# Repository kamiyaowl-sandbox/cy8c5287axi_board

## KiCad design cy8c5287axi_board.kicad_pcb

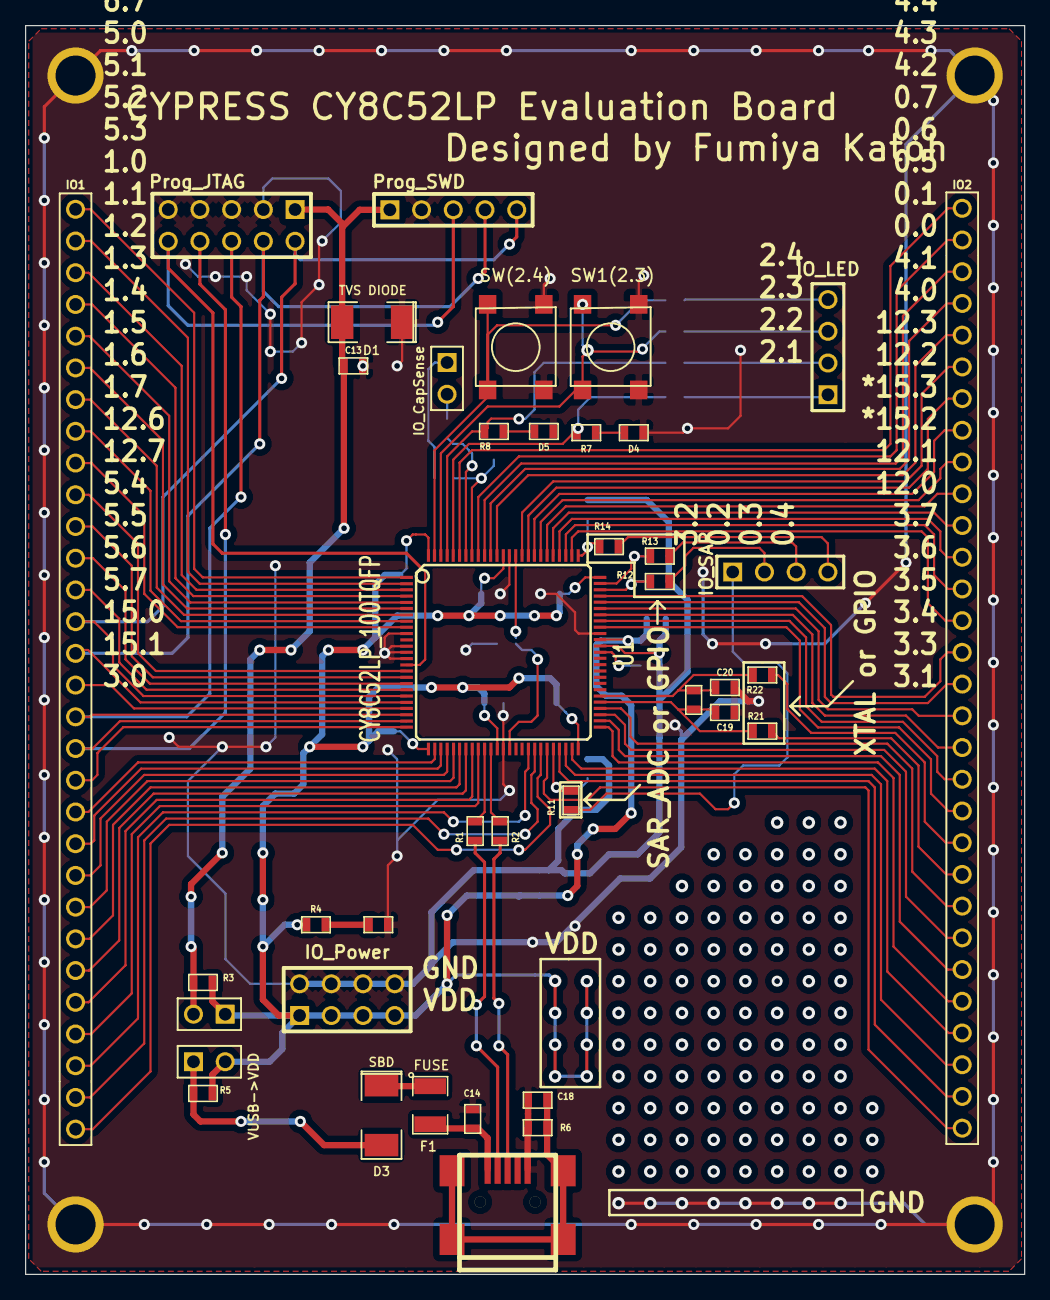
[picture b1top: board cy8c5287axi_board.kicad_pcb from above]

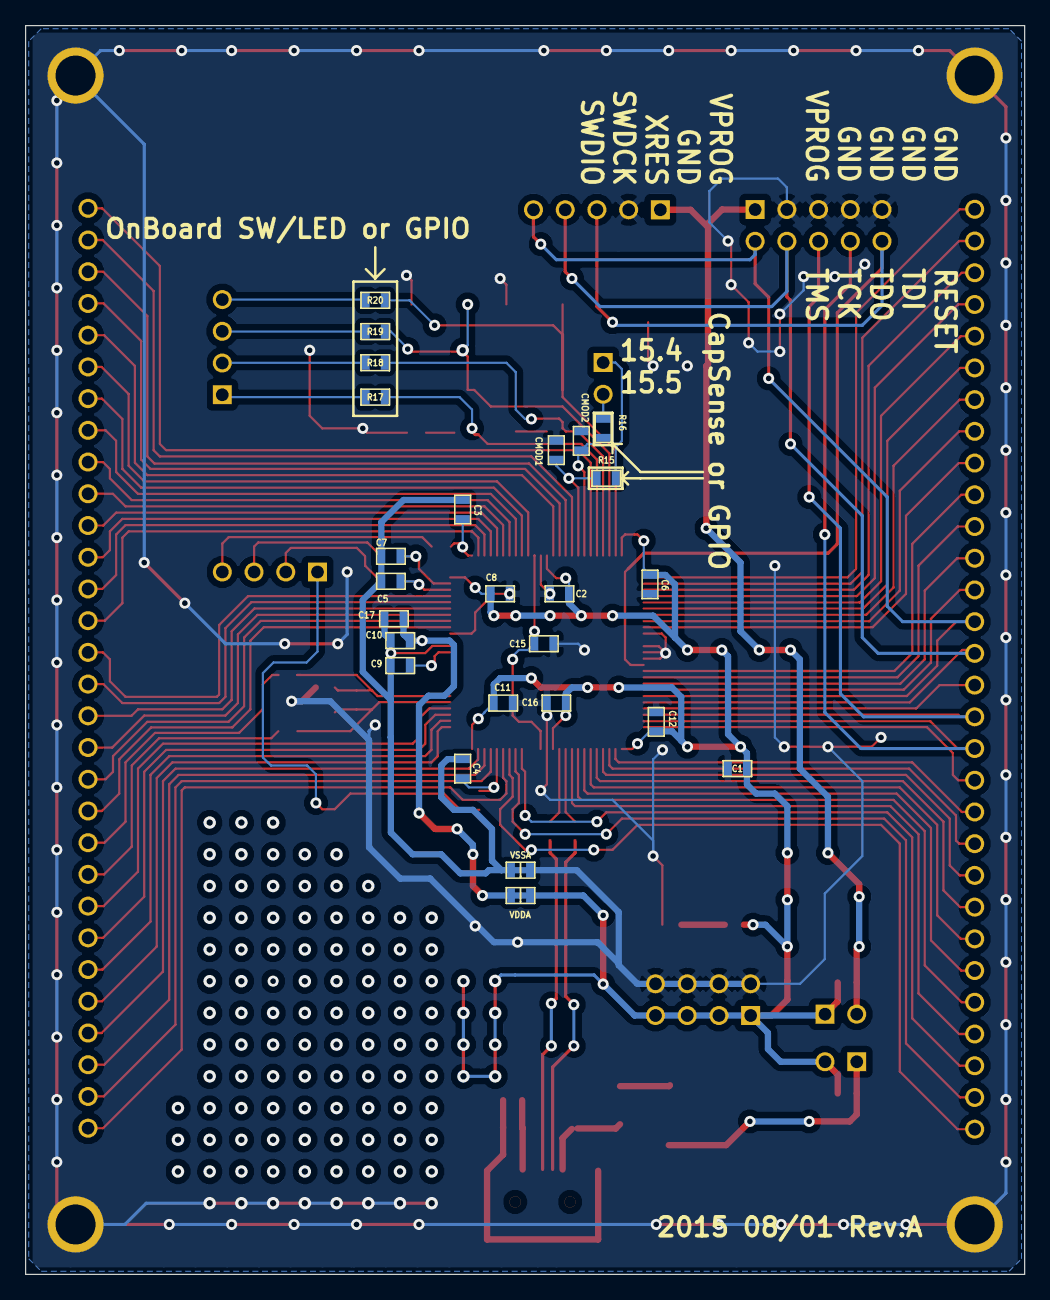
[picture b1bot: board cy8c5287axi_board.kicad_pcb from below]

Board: 2 copper layers, 80.0 x 100.0 mm, 61 parts (25 on the bottom side), 98 nets.

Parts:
C1, C3, C4, C5, C7, C9, C15, C17: 1u; SM0603
C2, C6, C8, C10, C11, C12, C13, C14, C16: 0.1u; SM0603
C18: 0.01u; SM0603
C19, C20: 22p; SM0603
CMOD1, CMOD2: 2200P; SM0603
D1: TVS DIODE; SM2010
D3: SBD; SM2010
D4: LED(2.1); SM0603
D5: LED(2.2); SM0603
F1: FUSE; SM1210
IO1, IO2: PIN_ARRAY_30
IO_CapSense: PIN_ARRAY_2X1
IO_LED: PIN_ARRAY_4x1
IO_Power: pin_array_4x2
IO_SAR: PIN_ARRAY_4x1
Prog_JTAG: PIN_ARRAY_5x2
Prog_SWD: PIN_ARRAY_5x1
R1, R2: 22; SM0603
R3, R5, R11, R12, R13, R14, R15, R16, R17, R18, R19, R20, R21, R22: 0; SM0603
R4: SM0603
R6: 100k; SM0603
R7, R8: R; SM0603
SW1(2.3): TSHA-T-2
SW(2.4): TSHA-T-2
U1: CY8C52LP_100TQFP; 100TQFP
VDDA: SM0603_Contact
VSSA: SM0603_Contact
VUSB->VDD: PIN_ARRAY_2X1

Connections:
/0.0: IO2.15, U1.71
/0.1: IO2.16, U1.72
/0.2*: C5.1, R12.1, U1.73
/0.3*: C7.1, R13.1, U1.74
/0.4*: C3.1, R14.1, U1.76
/0.5: IO2.17, U1.77
/0.6: IO2.18, U1.78
/0.7: IO2.19, U1.79
/1.0: IO1.14, Prog_JTAG.2, Prog_SWD.5, U1.20
/1.1: IO1.15, Prog_JTAG.4, Prog_SWD.4, U1.21
/1.2: IO1.16, U1.22
/1.3: IO1.17, Prog_JTAG.6, U1.23
/1.4: IO1.18, Prog_JTAG.8, U1.24
/1.5: IO1.19, U1.25
/1.6: IO1.20, U1.27
/1.7: IO1.21, U1.28
/2.0: IO2.30, U1.95
/2.1+: R7.1, R17.1, U1.96
/2.2+: R8.1, R18.1, U1.97
/2.3+: R19.1, SW1(2.3).1, U1.98
/2.4+: R20.1, SW(2.4).1, U1.99
/2.5: IO1.1, U1.1
/2.6: IO1.2, U1.2
/2.7: IO1.3, U1.3
/3.0: IO1.30, U1.44
/3.1: IO2.1, U1.45
/3.2*: C4.1, R11.1, U1.46
/3.3: IO2.2, U1.47
/3.4: IO2.3, U1.48
/3.5: IO2.4, U1.49
/3.6: IO2.5, U1.51
/3.7: IO2.6, U1.52
/4.0: IO2.13, U1.69
/4.1: IO2.14, U1.70
/4.2: IO2.20, U1.80
/4.3: IO2.21, U1.81
/4.4: IO2.22, U1.82
/4.5: IO2.23, U1.83
/4.6: IO2.24, U1.84
/4.7: IO2.25, U1.85
/5.0: IO1.10, U1.16
/5.1: IO1.11, U1.17
/5.2: IO1.12, U1.18
/5.3: IO1.13, U1.19
/5.4: IO1.24, U1.31
/5.5: IO1.25, U1.32
/5.6: IO1.26, U1.33
/5.7: IO1.27, U1.34
/6.0: IO2.26, U1.89
/6.1: IO2.27, U1.90
/6.2: IO2.28, U1.91
/6.3: IO2.29, U1.92
/6.4: IO1.6, U1.6
/6.5: IO1.7, U1.7
/6.6: IO1.8, U1.8
/6.7: IO1.9, U1.9
/12.0: IO2.7, U1.53
/12.1: IO2.8, U1.54
/12.2: IO2.11, U1.67
/12.3: IO2.12, U1.68
/12.4: IO1.4, U1.4
/12.5: IO1.5, U1.5
/12.6: IO1.22, U1.29
/12.7: IO1.23, U1.30
/15.0: IO1.28, U1.42
/15.1: IO1.29, U1.43
/15.2*: IO2.9, R21.1
/15.3*: IO2.10, R22.1
/15.4*: CMOD1.1, R15.1, U1.93
/15.5*: CMOD2.1, R16.1, U1.94
/15.6*: R1.1, U1.35
/15.7*: R2.1, U1.36
//XRES: Prog_JTAG.10, Prog_SWD.3, U1.15
/kHz_XI: C20.1, R22.2, U1.56
/kHz_XO: C19.1, R21.2, U1.55
unnamed: D4.1, R7.2
unnamed: D5.1, R8.2
unnamed: IO_CapSense.1, R15.2
unnamed: IO_CapSense.2, R16.2
unnamed: IO_LED.1, R17.2
unnamed: IO_LED.2, R18.2
unnamed: IO_LED.3, R19.2
unnamed: IO_LED.4, R20.2
unnamed: IO_SAR.4, R14.2
unnamed: IO_SAR.1, R11.2
unnamed: IO_SAR.2, R12.2
unnamed: IO_SAR.3, R13.2
unnamed: D3.2, R5.2, VUSB->VDD.1
unnamed: D3.1, F1.1
unnamed: C14.1, F1.2
unnamed: C18.1, R6.1
VCCA: C9.2, U1.63
VCCD: C15.2, U1.39, U1.86
VDDA: C10.1, C17.1, U1.65, VDDA.2
VDDD: C1.1, C2.1, C6.1, C8.1, C11.1, C12.1, C16.1, IO_Power.1, IO_Power.3, IO_Power.5, IO_Power.7, R3.2, R4.1, R5.1, U1.26, U1.37, U1.50, U1.75, U1.88, U1.100, VDDA.1, VUSB->VDD.2
VPROG: C13.1, D1.2, Prog_JTAG.1, Prog_SWD.1, R3.1
VSSA: C3.2, C4.2, C5.2, C7.2, C9.1, C10.2, C17.2, U1.64, VSSA.2
VSSD: C1.2, C2.2, C6.2, C8.2, C11.2, C12.2, C13.2, C14.2, C15.1, C16.2, C18.2, C19.2, C20.2, CMOD1.2, CMOD2.2, D1.1, D4.2, D5.2, IO_Power.2, IO_Power.4, IO_Power.6, IO_Power.8, Prog_JTAG.3, Prog_JTAG.5, Prog_JTAG.7, Prog_JTAG.9, Prog_SWD.2, R6.2, SW1(2.3).2, SW(2.4).2, U1.10, U1.12, U1.13, U1.14, U1.38, U1.66, U1.87, VSSA.1

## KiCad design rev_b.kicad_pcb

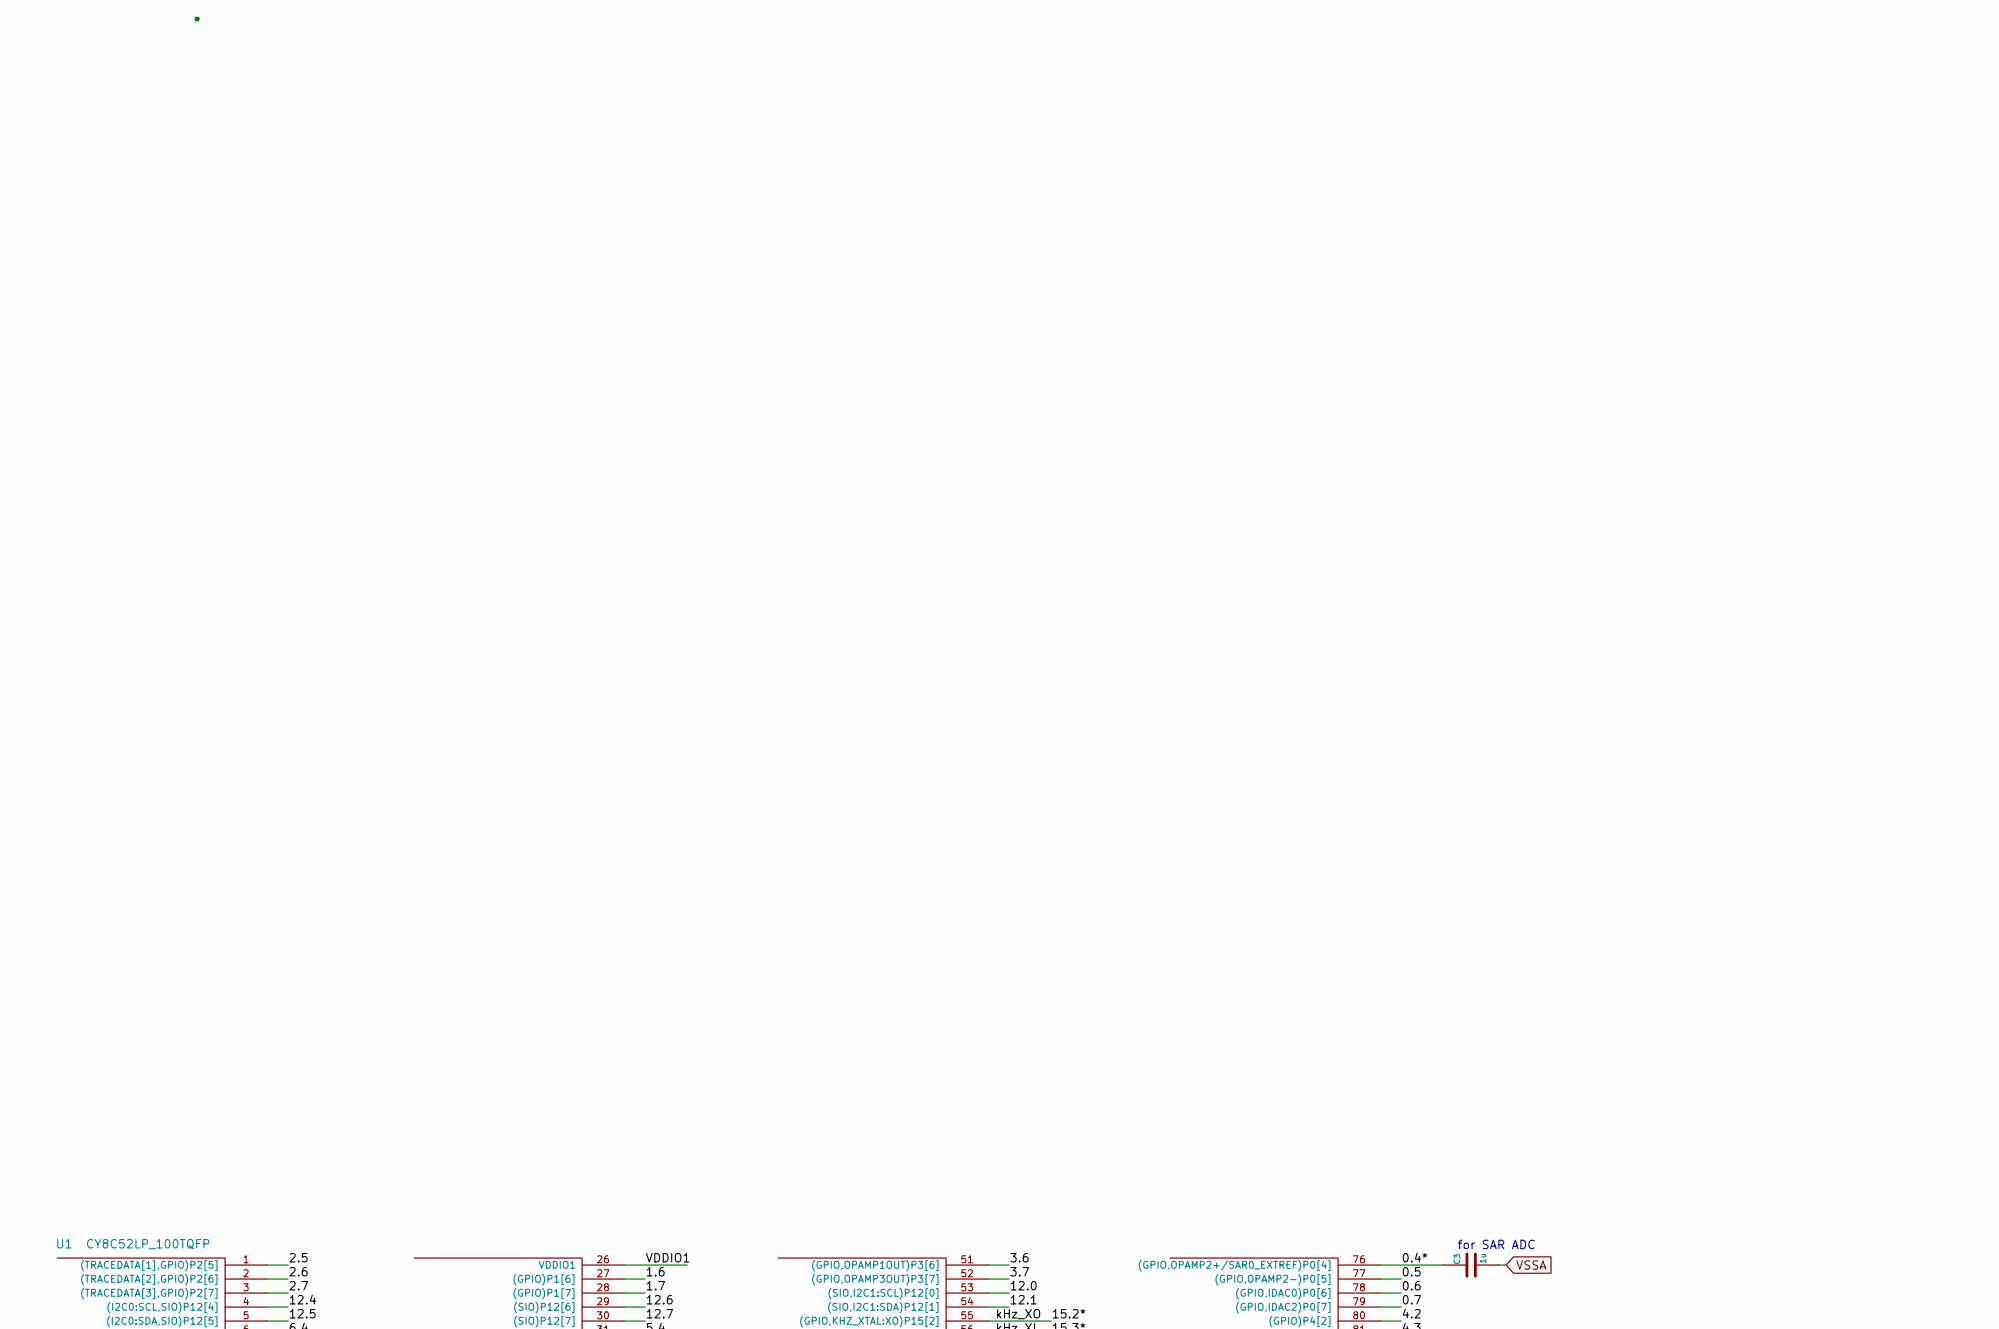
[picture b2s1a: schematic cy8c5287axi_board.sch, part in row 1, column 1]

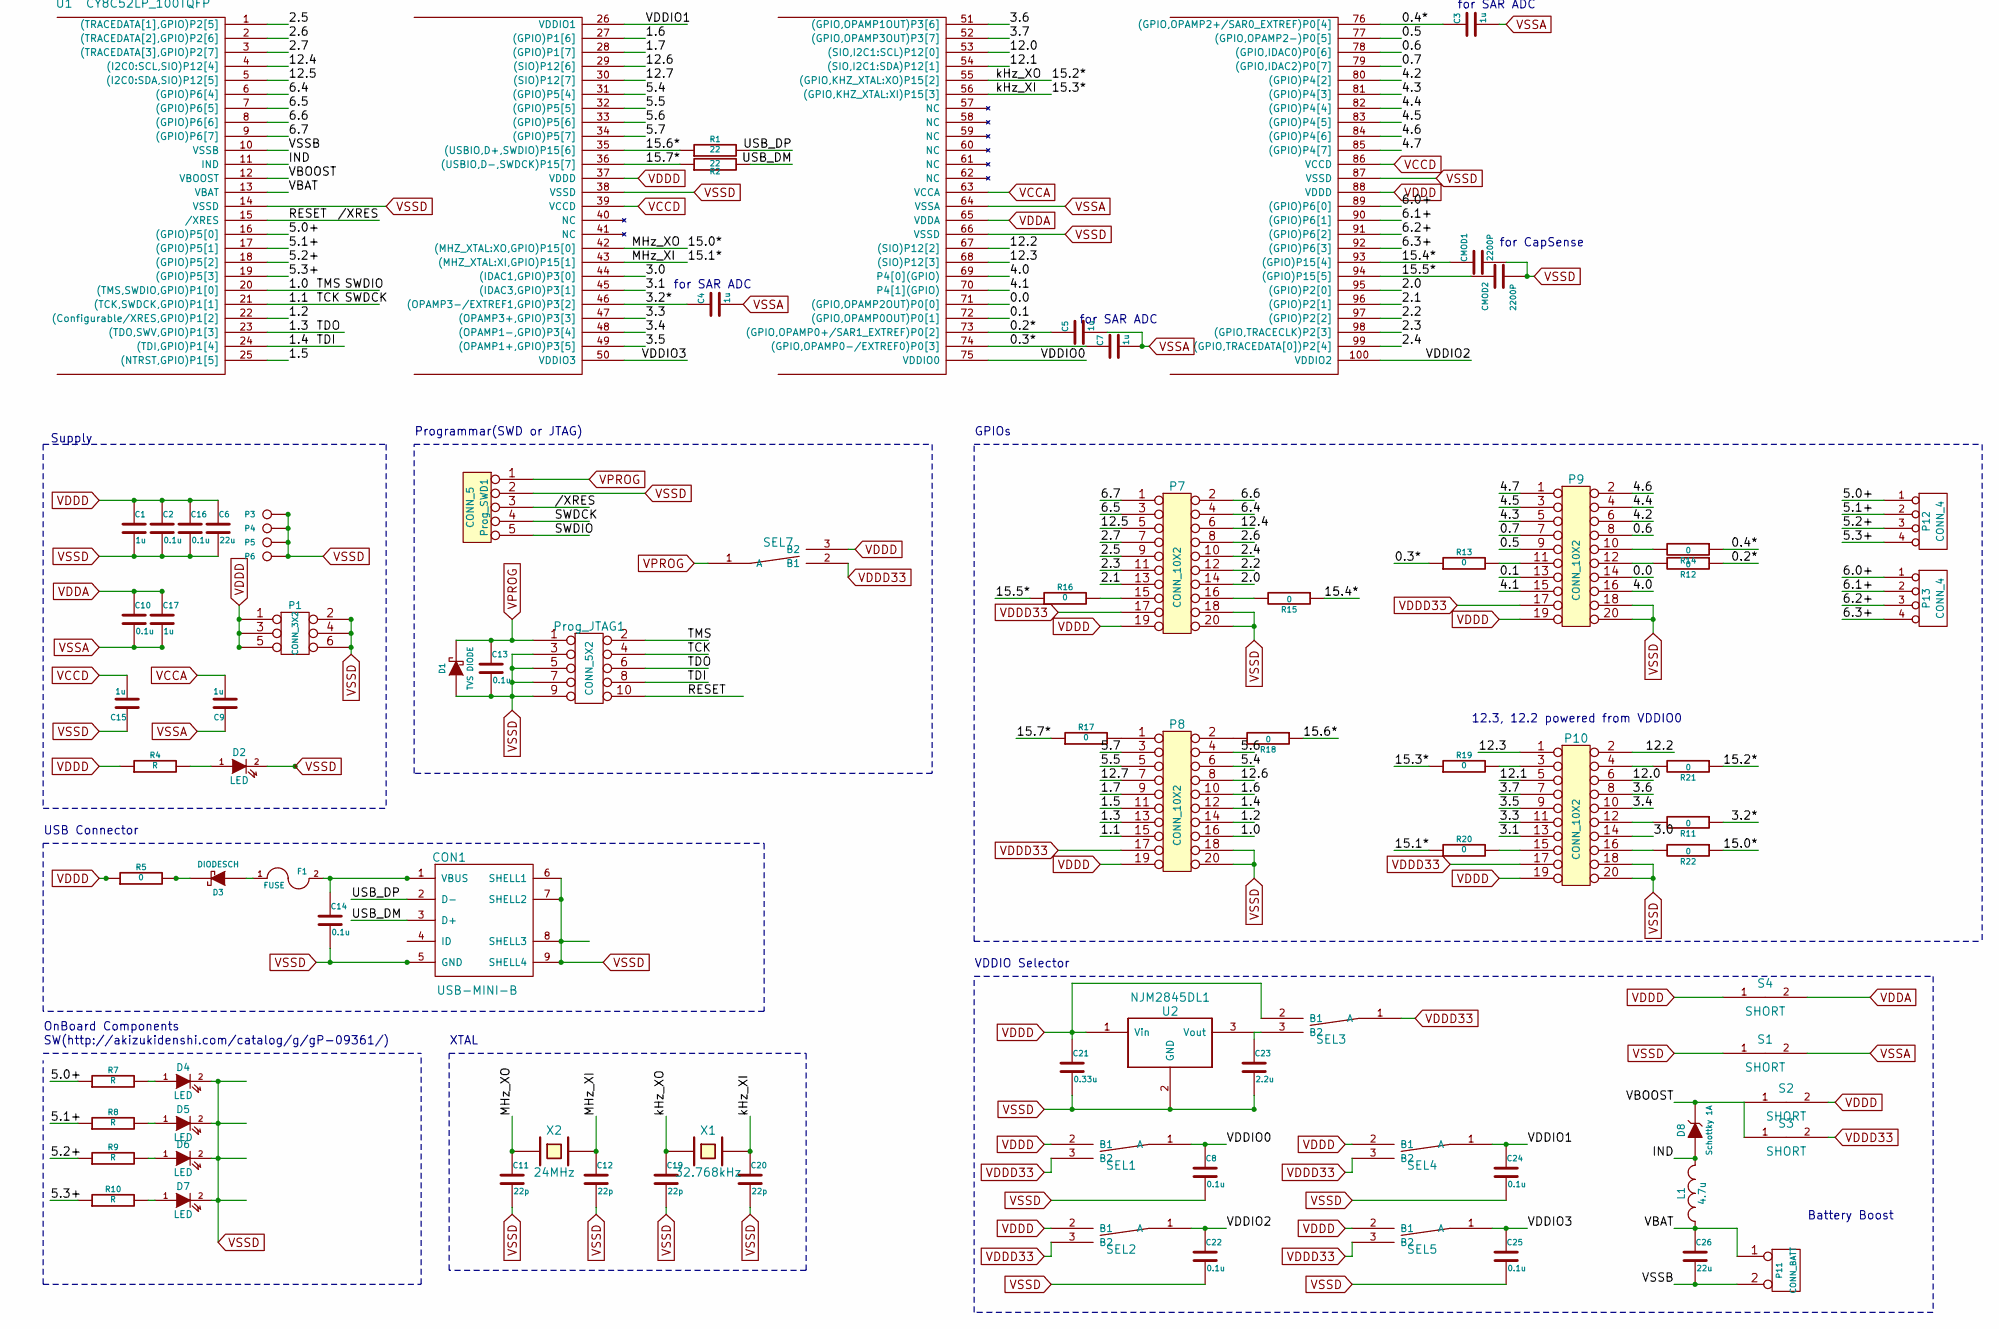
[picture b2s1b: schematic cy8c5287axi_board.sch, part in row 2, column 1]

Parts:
C1, C3, C4, C5, C7, C9, C15, C17: 1u
C2, C8, C10, C13, C14, C16, C22, C24, C25: 0.1u
C6, C26: 22u
C11, C12, C19, C20: 22p
C21: 0.33u
C23: 2.2u
CMOD1, CMOD2: 2200P
CON1: USB-MINI-B
D1: TVS DIODE
D2, D4, D5, D6, D7: LED
D3: DIODESCH
D8: Schottky 1A
F1: FUSE
L1: 4.7u
P1: CONN_3X2
P3, P4, P5, P6: CONN_1
P7, P8, P9, P10: CONN_10X2
P11: CONN_BATT
P12, P13: CONN_4
Prog_JTAG1: CONN_5X2
Prog_SWD1: CONN_5
R1, R2: 22
R4, R7, R8, R9, R10: R
R5, R11, R12, R13, R14, R15, R16, R17, R18, R19, R20, R21, R22: 0
S1, S2, S3, S4: SHORT
SEL1, SEL2, SEL3, SEL4, SEL5, SEL7: SEL
U1: CY8C52LP_100TQFP
U2: NJM2845DL1
X1: 32.768kHz
X2: 24MHz

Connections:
/0.0: P9.14, U1.71 ((GPIO,OPAMP2OUT)P0[0])
/0.1: P9.13, U1.72 ((GPIO,OPAMP0OUT)P0[1])
/0.2*: C5.1, R12.1, U1.73 ((GPIO,OPAMP0+/SAR1_EXTREF)P0[2])
/0.3*: C7.1, R13.1, U1.74 ((GPIO,OPAMP0-/EXTREF0)P0[3])
/0.4*: C3.1, R14.1, U1.76 ((GPIO,OPAMP2+/SAR0_EXTREF)P0[4])
/0.5: P9.9, U1.77 ((GPIO,OPAMP2-)P0[5])
/0.6: P9.8, U1.78 ((GPIO,IDAC0)P0[6])
/0.7: P9.7, U1.79 ((GPIO,IDAC2)P0[7])
/1.0: P8.16, Prog_JTAG1.2, Prog_SWD1.5, U1.20 ((TMS,SWDIO,GPIO)P1[0])
/1.1: P8.15, Prog_JTAG1.4, Prog_SWD1.4, U1.21 ((TCK,SWDCK,GPIO)P1[1])
/1.2: P8.14, U1.22 ((Configurable/XRES,GPIO)P1[2])
/1.3: P8.13, Prog_JTAG1.6, U1.23 ((TDO,SWV,GPIO)P1[3])
/1.4: P8.12, Prog_JTAG1.8, U1.24 ((TDI,GPIO)P1[4])
/1.5: P8.11, U1.25 ((NTRST,GPIO)P1[5])
/1.6: P8.10, U1.27 ((GPIO)P1[6])
/1.7: P8.9, U1.28 ((GPIO)P1[7])
/2.0: P7.14, U1.95 ((GPIO)P2[0])
/2.1: P7.13, U1.96 ((GPIO)P2[1])
/2.2: P7.12, U1.97 ((GPIO)P2[2])
/2.3: P7.11, U1.98 ((GPIO,TRACECLK)P2[3])
/2.4: P7.10, U1.99 ((GPIO,TRACEDATA[0])P2[4])
/2.5: P7.9, U1.1 ((TRACEDATA[1],GPIO)P2[5])
/2.6: P7.8, U1.2 ((TRACEDATA[2],GPIO)P2[6])
/2.7: P7.7, U1.3 ((TRACEDATA[3],GPIO)P2[7])
/3.0: P10.14, U1.44 ((IDAC1,GPIO)P3[0])
/3.1: P10.13, U1.45 ((IDAC3,GPIO)P3[1])
/3.2*: C4.1, R11.1, U1.46 ((OPAMP3-/EXTREF1,GPIO)P3[2])
/3.3: P10.11, U1.47 ((OPAMP3+,GPIO)P3[3])
/3.4: P10.10, U1.48 ((OPAMP1-,GPIO)P3[4])
/3.5: P10.9, U1.49 ((OPAMP1+,GPIO)P3[5])
/3.6: P10.8, U1.51 ((GPIO,OPAMP1OUT)P3[6])
/3.7: P10.7, U1.52 ((GPIO,OPAMP3OUT)P3[7])
/4.0: P9.16, U1.69 (P4[0](GPIO))
/4.1: P9.15, U1.70 (P4[1](GPIO))
/4.2: P9.6, U1.80 ((GPIO)P4[2])
/4.3: P9.5, U1.81 ((GPIO)P4[3])
/4.4: P9.4, U1.82 ((GPIO)P4[4])
/4.5: P9.3, U1.83 ((GPIO)P4[5])
/4.6: P9.2, U1.84 ((GPIO)P4[6])
/4.7: P9.1, U1.85 ((GPIO)P4[7])
/5.0+: P12.1, R7.1, U1.16 ((GPIO)P5[0])
/5.1+: P12.2, R8.1, U1.17 ((GPIO)P5[1])
/5.2+: P12.3, R9.1, U1.18 ((GPIO)P5[2])
/5.3+: P12.4, R10.1, U1.19 ((GPIO)P5[3])
/5.4: P8.6, U1.31 ((GPIO)P5[4])
/5.5: P8.5, U1.32 ((GPIO)P5[5])
/5.6: P8.4, U1.33 ((GPIO)P5[6])
/5.7: P8.3, U1.34 ((GPIO)P5[7])
/6.0+: P13.1, U1.89 ((GPIO)P6[0])
/6.1+: P13.2, U1.90 ((GPIO)P6[1])
/6.2+: P13.3, U1.91 ((GPIO)P6[2])
/6.3+: P13.4, U1.92 ((GPIO)P6[3])
/6.4: P7.4, U1.6 ((GPIO)P6[4])
/6.5: P7.3, U1.7 ((GPIO)P6[5])
/6.6: P7.2, U1.8 ((GPIO)P6[6])
/6.7: P7.1, U1.9 ((GPIO)P6[7])
/12.0: P10.6, U1.53 ((SIO,I2C1:SCL)P12[0])
/12.1: P10.5, U1.54 ((SIO,I2C1:SDA)P12[1])
/12.2: P10.2, U1.67 ((SIO)P12[2])
/12.3: P10.1, U1.68 ((SIO)P12[3])
/12.4: P7.6, U1.4 ((I2C0:SCL,SIO)P12[4])
/12.5: P7.5, U1.5 ((I2C0:SDA,SIO)P12[5])
/12.6: P8.8, U1.29 ((SIO)P12[6])
/12.7: P8.7, U1.30 ((SIO)P12[7])
/15.0*: C11.1, R22.1, U1.42 ((MHZ_XTAL:XO,GPIO)P15[0]), X2.1
/15.1*: C12.1, R20.1, U1.43 ((MHZ_XTAL:XI,GPIO)P15[1]), X2.2
/15.2*: C19.1, R21.1, U1.55 ((GPIO,KHZ_XTAL:XO)P15[2]), X1.1
/15.3*: C20.1, R19.1, U1.56 ((GPIO,KHZ_XTAL:XI)P15[3]), X1.2
/15.4*: CMOD1.1, R15.1, U1.93 ((GPIO)P15[4])
/15.5*: CMOD2.1, R16.1, U1.94 ((GPIO)P15[5])
/15.6*: R1.1, R18.1, U1.35 ((USBIO,D+,SWDIO)P15[6])
/15.7*: R2.1, R17.1, U1.36 ((USBIO,D-,SWDCK)P15[7])
//XRES: Prog_JTAG1.10, Prog_SWD1.3, U1.15 (/XRES)
/IND: D8.1 (A), L1.2, U1.11 (IND)
/USB_DM: CON1.3 (D+), R2.2
/USB_DP: CON1.2 (D-), R1.2
/VBAT: C26.1, L1.1, P11.1, U1.13 (VBAT)
/VBOOST: D8.2 (K), S2.1, S3.1, U1.12 (VBOOST)
/VDDIO0: C8.1, SEL1.1 (A), U1.75 (VDDIO0)
/VDDIO1: C24.1, SEL4.1 (A), U1.26 (VDDIO1)
/VDDIO2: C22.1, SEL2.1 (A), U1.100 (VDDIO2)
/VDDIO3: C25.1, SEL5.1 (A), U1.50 (VDDIO3)
/VSSB: C26.2, P11.2 (PM), U1.10 (VSSB)
unnamed: D4.1 (A), R7.2
unnamed: D5.1 (A), R8.2
unnamed: D2.1 (A), R4.2
unnamed: C23.1, SEL3.3 (B2), U2.3 (Vout)
unnamed: D3.2 (K), R5.2
unnamed: D3.1 (A), F1.1
unnamed: C14.1, CON1.1 (VBUS), F1.2
unnamed: D6.1 (A), R9.2
unnamed: D7.1 (A), R10.2
unnamed: P7.15, R16.2
unnamed: P7.16, R15.2
unnamed: P9.10, R14.2
unnamed: P9.11, R13.2
unnamed: P9.12, R12.2
unnamed: P8.2, R18.2
unnamed: P8.1, R17.2
unnamed: P10.3, R19.2
unnamed: P10.15, R20.2
unnamed: P10.4, R21.2
unnamed: P10.12, R11.2
unnamed: P10.16, R22.2
VCCA: C9.2, U1.63 (VCCA)
VCCD: C15.2, U1.39 (VCCD), U1.86 (VCCD)
VDDA: C10.1, C17.1, S4.2, U1.65 (VDDA)
VDDD: C1.1, C2.1, C6.1, C16.1, C21.1, P1.1, P1.3, P1.5, P7.19, P8.19, P9.19, P10.19, R4.1, R5.1, S2.2, S4.1, SEL1.2 (B1), SEL2.2 (B1), SEL3.2 (B1), SEL4.2 (B1), SEL5.2 (B1), SEL7.3 (B2), U1.37 (VDDD), U1.88 (VDDD), U2.1 (Vin)
VDDD33: P7.17, P8.17, P9.17, P10.17, S3.2, SEL1.3 (B2), SEL2.3 (B2), SEL3.1 (A), SEL4.3 (B2), SEL5.3 (B2), SEL7.2 (B1)
VPROG: C13.1, D1.2 (K), Prog_JTAG1.1, Prog_SWD1.1, SEL7.1 (A)
VSSA: C3.2, C4.2, C5.2, C7.2, C9.1, C10.2, C17.2, S1.2, U1.64 (VSSA)
VSSD: C1.2, C2.2, C6.2, C8.2, C11.2, C12.2, C13.2, C14.2, C15.1, C16.2, C19.2, C20.2, C21.2, C22.2, C23.2, C24.2, C25.2, CMOD1.2, CMOD2.2, CON1.5 (GND), CON1.6 (SHELL1), CON1.7 (SHELL2), CON1.8 (SHELL3), CON1.9 (SHELL4), D1.1 (A), D2.2 (K), D4.2 (K), D5.2 (K), D6.2 (K), D7.2 (K), P1.2, P1.4, P1.6, P3.1, P4.1, P5.1, P6.1, P7.18, P7.20, P8.18, P8.20, P9.18, P9.20, P10.18, P10.20, Prog_JTAG1.3, Prog_JTAG1.5, Prog_JTAG1.7, Prog_JTAG1.9, Prog_SWD1.2, S1.1, U1.14 (VSSD), U1.38 (VSSD), U1.66 (VSSD), U1.87 (VSSD), U2.2 (GND)

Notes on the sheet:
Programmar(SWD or JTAG)
Supply
USB Connector
for CapSense
for SAR ADC
OnBoard Components
SW(http://akizukidenshi.com/catalog/g/gP-09361/)
GPIOs
VDDIO Selector
XTAL
12.3, 12.2 powered from VDDIO0
Battery Boost

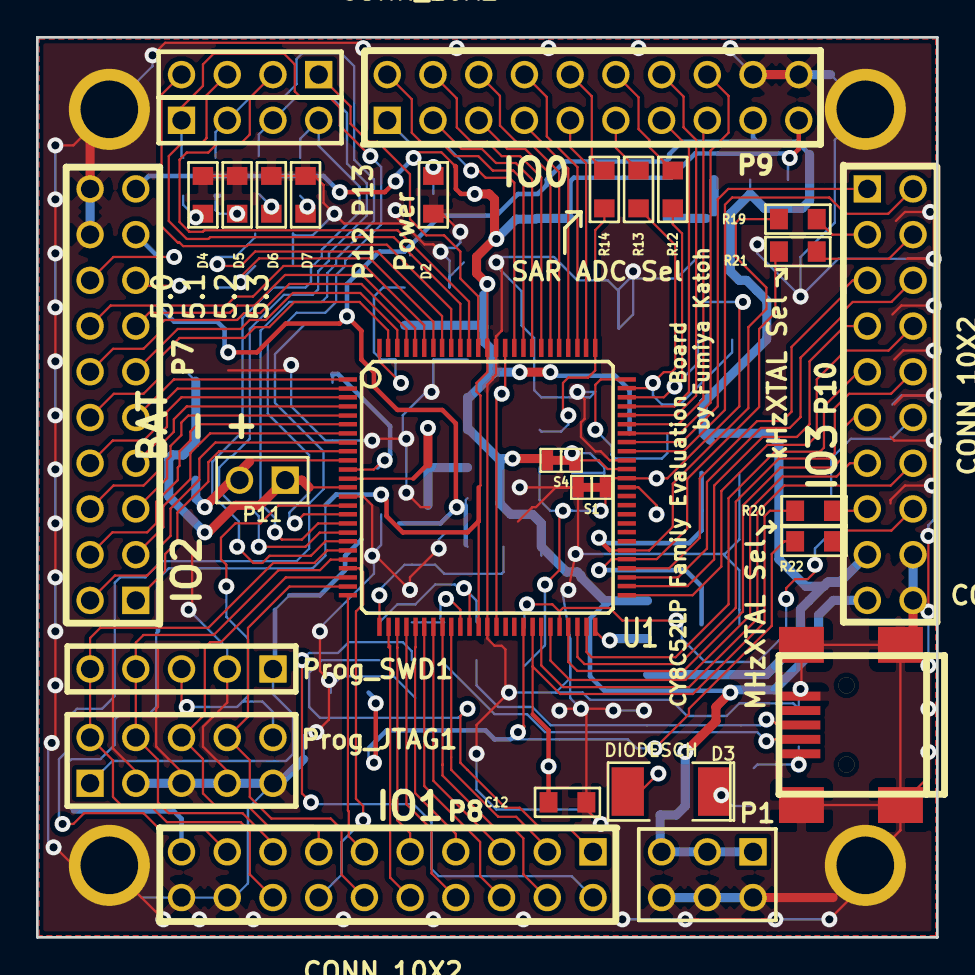
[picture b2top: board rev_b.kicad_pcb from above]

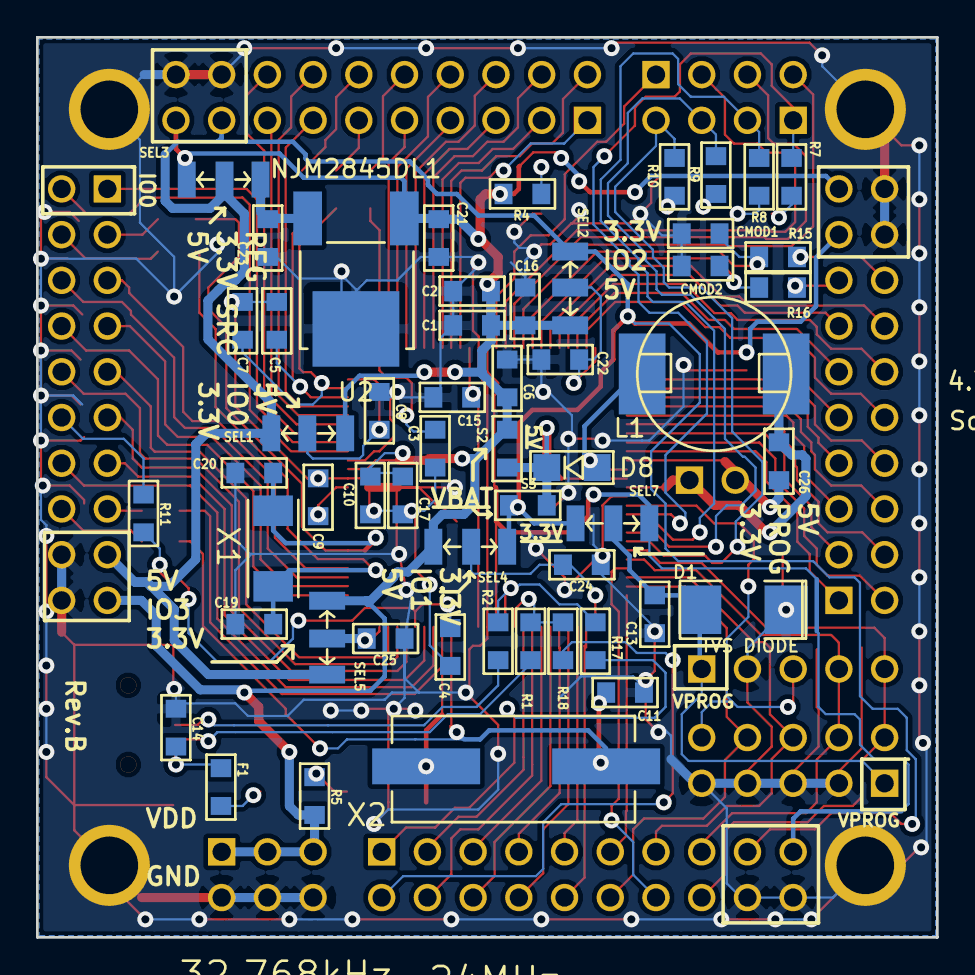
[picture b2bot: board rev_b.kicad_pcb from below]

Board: 2 copper layers, 50.0 x 50.0 mm, 86 parts (54 on the bottom side), 112 nets.

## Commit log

2015-08-01 Create
2015-08-03 Tenaoshi siyou
2015-09-28 revB create
2015-09-28 Fixed: ReturnPass
2015-09-29 Output: Rev.B
2015-10-08 Output
